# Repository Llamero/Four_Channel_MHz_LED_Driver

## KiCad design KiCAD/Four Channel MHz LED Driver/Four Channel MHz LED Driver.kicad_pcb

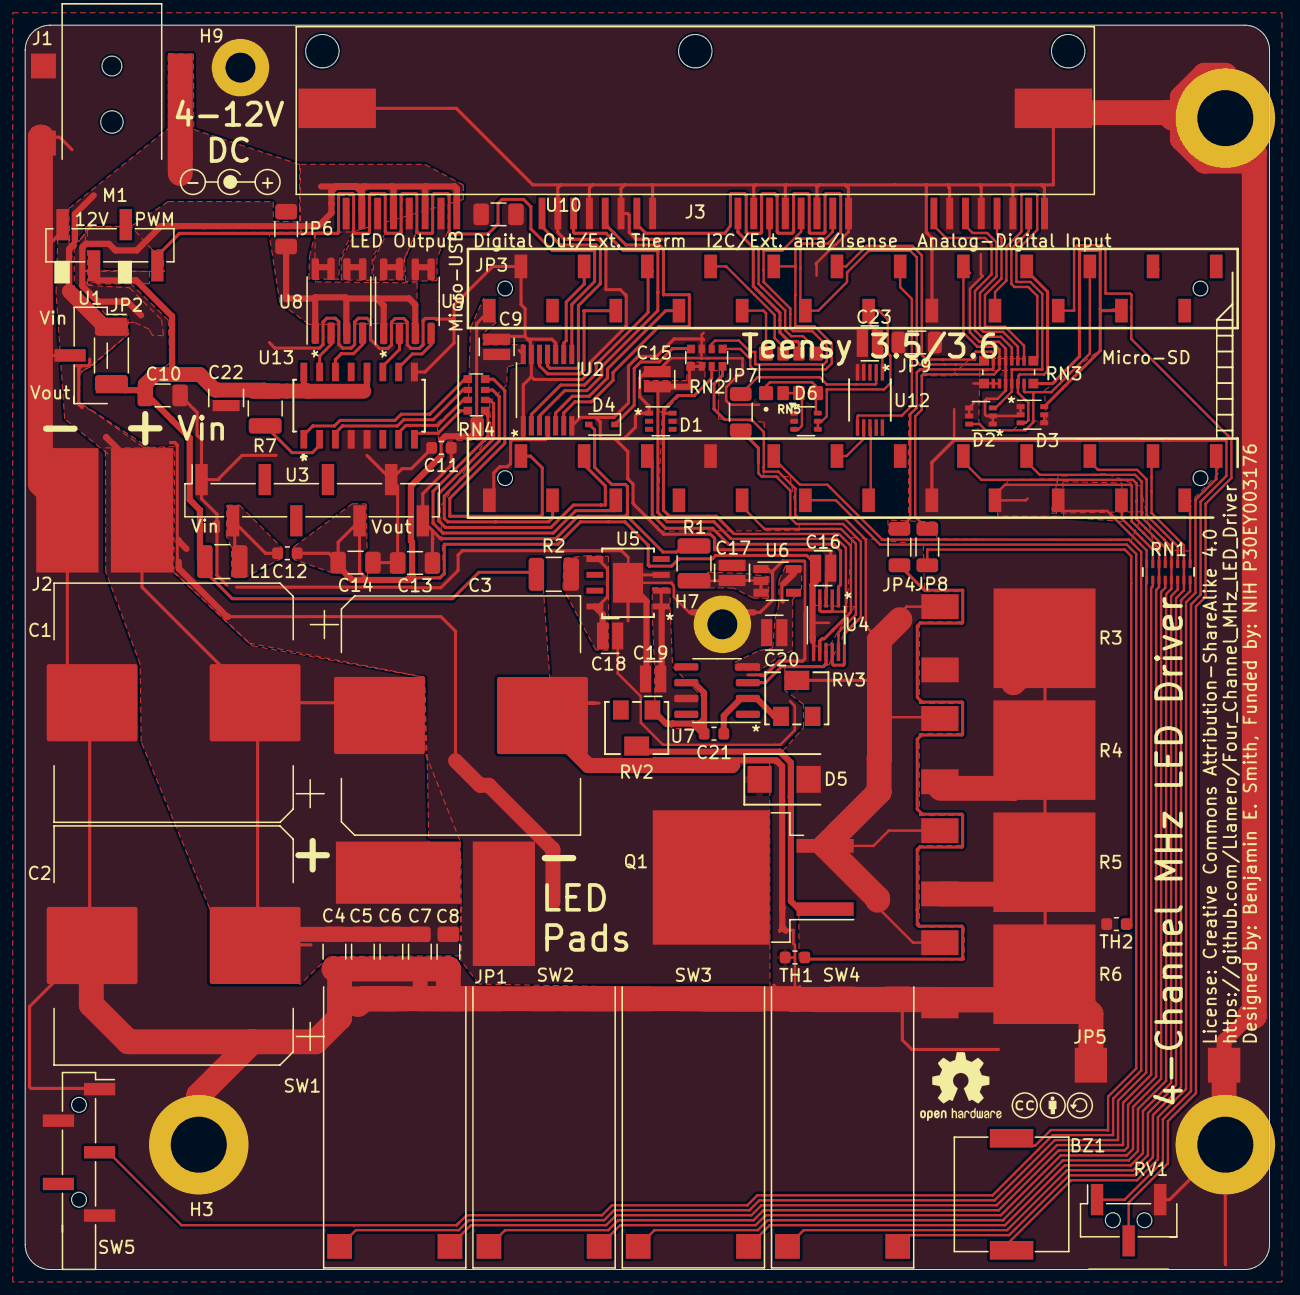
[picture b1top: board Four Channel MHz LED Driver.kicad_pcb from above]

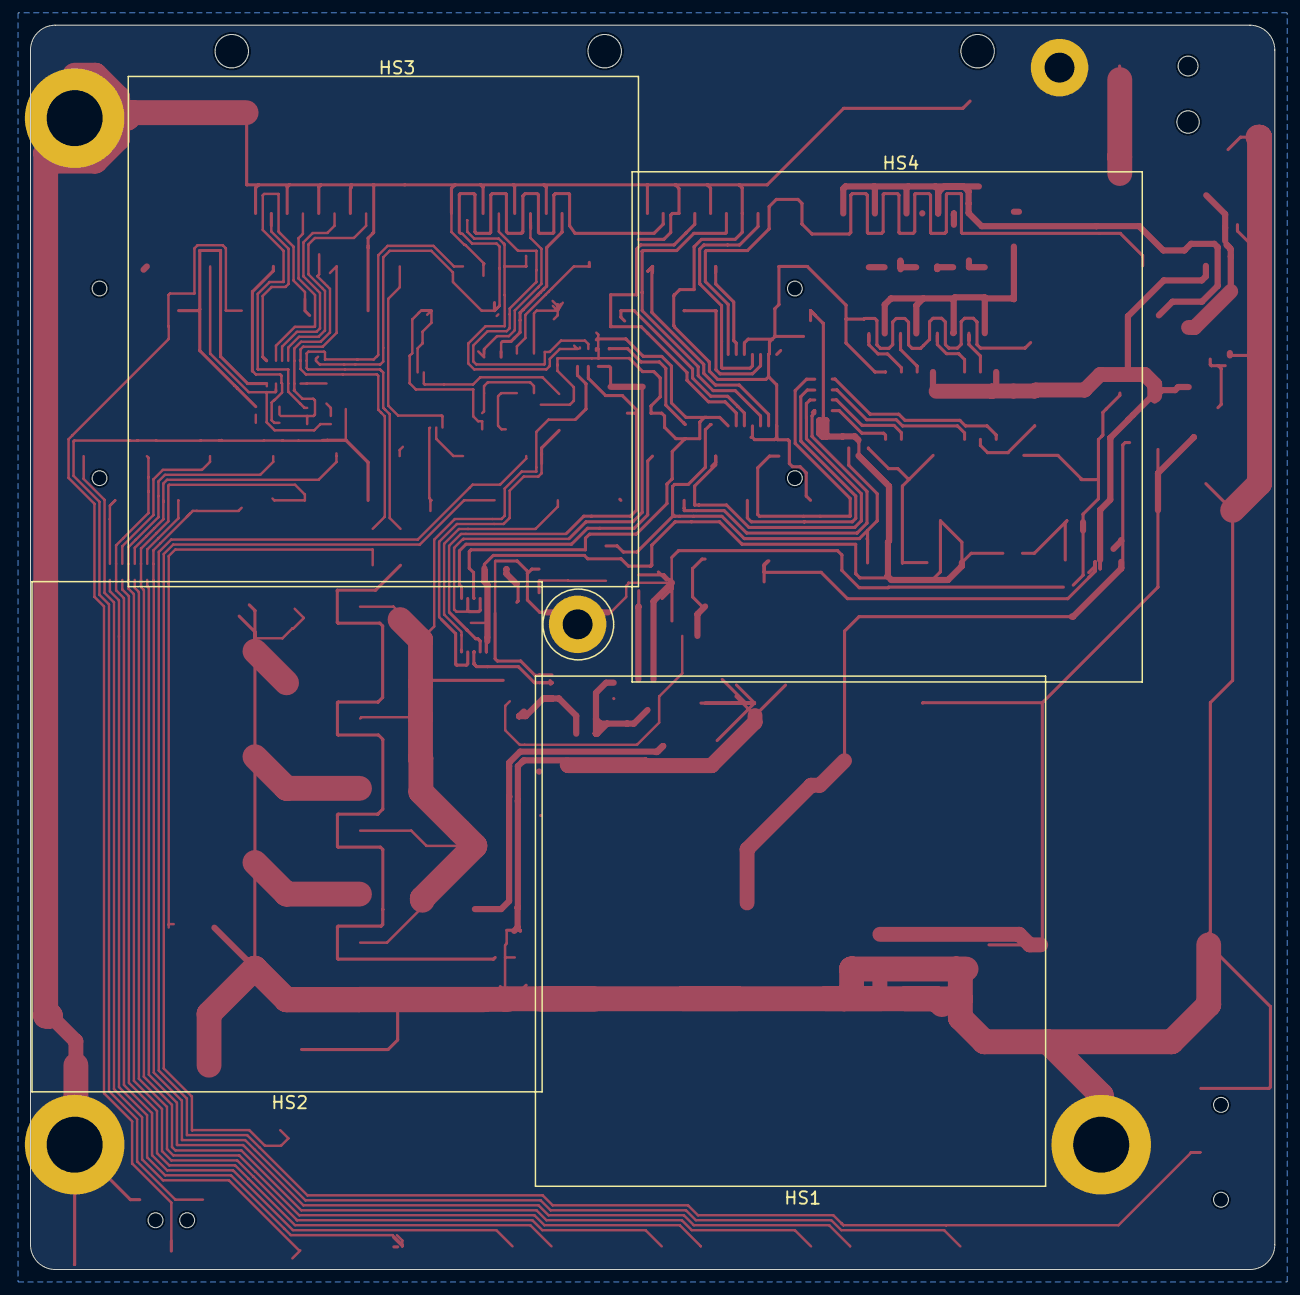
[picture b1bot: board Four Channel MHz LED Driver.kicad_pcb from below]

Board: 2 copper layers, 100.0 x 100.0 mm, 89 parts (4 on the bottom side), 86 nets.

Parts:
BZ1: CPT-2016-75-SMT-TR; SMT-0940-T-3V-R_9x9_alarm
C1, C2, C3: 7500uF; CP_Elec_18x22-EEE-FK1C752SV
C4, C5, C6, C7, C8, C10, C13, C14: 47uF; C_1206_3216Metric
C9, C15, C16, C17, C18, C19, C20, C22, C23: 2.2uF; 0508_Capacitor
C11, C12, C21: 2200pF; C_0603_1608Metric
D1, D2, D3, D6: BAT54BRW; SOT-363_SC-70-6
D4: D_Zener; D_SOD-323
D5: TVS_Diode; DO-214AA
H3: MountingHole_Pad; NF-A9_with_standoffs_and_bolts
H7, H9: MountingHole_Pad; M2_standoff_ground_via
HS1, HS2, HS3, HS4: HS-PCB; Heatsink_910-40-2-23-2-B-0
J1: Barrel_Jack_Switch; DC-jack_54-00165
J2: Conn_01x02_Female; Wire_Pad
J3: 8P8C_Shielded_x4; RJ45_x4-RJSSE-5380-04
JP1: LED wire; L-Wire_Pad
JP2: Jumper_NC_Small; R_2010_5025Metric
JP3, JP4, JP6, JP7, JP8, JP9: Jumper_NC_Small; R_1206_3216Metric
JP5: Jumper_NC_Small; 20A_shunt_5104
L1: 10uH; L_1210_3225Metric
LOGO1: CC license; Creative_commons_license
LOGO2: Jack Polarity; Polarity_Center_Positive
LOGO3: OSHW Logo; OSHW-Logo2_7.3x6mm_SilkScreen
M1: Fan_4pin; 4-pin_fan_SMD
Q1: SUM70060E; TO-263-2
R1, R2, R7: 12; R_1210_3225Metric
R3, R4, R5, R6: 5; TO-252_resistor
RN1: 150; EXB-2HV151JV-1605x8
RN2, RN4: 200; R_Array_Convex_4x0612
RN3: 4.7k; 1506-EXB-2HV472JV-for_2_oz_pour
RN5: 4.7k; RESCAXS127P508X320X70-8N
RV1: R_POT; Pot_with_header
RV2, RV3: R_POT_TRIM; 3224W-1-502E
SW1, SW2, SW3, SW4: Pushbutton_with_LED; Pushbutton_LED-ELUMOATHQ3C12
SW5: SW_SPDT; 1x5_header_SSM-105-L-SV-BE-LC
TH1, TH2: Thermistor; R_0603_1608Metric
U1: 12V boost; 12V_DC-DC_with_header_2117
U2: SN74LV4T125PWR; SN74LV4T125
U3: DPBW06F-05; DPBW06F-05_with_header
U4: TMUX1204DGSR
U5: BDJ0GA5WEFJ-E2
U6: ADP7182AUJZ-1.8-R7; TSOT-23-5
U7: LT6200CS8-10; SOIC-8_3.9x4.9mm_P1.27mm
U8, U9: IRF9358TRPBF; SO-8_3.9x4.9mm_P1.27mm
U10: Teensy4.1; Teensy_4_1_with_headers
U12: DAC80501ZDGSR; DGS10_TEX
U13: EL7457CSZ-T7; EL7457CS

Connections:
/3.3V: C23.2, D1.5, D2.4, D2.5, D3.4, D3.5, D6.4, D6.5, RN3.9 (R8.2), RN3.10 (R7.2), RN3.11 (R6.2), RV1.1, U10.8 (6_OUT1D), U10.15 (3V3), U10.36 (14_A0_TX3_SPDIF_OUT), U10.46 (3V3), U12.1 (VDD)
/5V: C9.1, C12.1, C14.2, C16.2, U2.14 (VCC), U3.6 (+Vout), U4.5 (EN), U4.6 (VDD), U10.48 (VIN)
/5V_fan_PWM: M1.4 (PWM), U2.8 (3Y)
/10V-analog: C19.1, U5.1 (VO), U5.2 (FB), U7.7 (V+)
/12V: C10.2, C22.2, JP2.1, L1.1, M1.2 (+), R2.1, R7.1, U1.3 (OUT), U13.12 (VH), U13.16 (VS+)
/-0.25V_analog: C15.1, RN2.5 (R4.2), RN2.6 (R3.2), U4.2 (S1), U4.4 (S3)
/-1.8V-analog: C20.2, U6.5 (VOUT), U7.4 (V-)
/-5V: C11.1, C13.1, D4.2 (A), R1.1, U3.8 (-Vout)
/A-D_input_1: D2.3, RN3.13 (R4.2), U10.32 (40_A16)
/A-D_input_2: D3.3, RN3.14 (R3.2), U10.31 (39_MISO1_OUT1A)
/A-D_input_3: D2.6, RN3.15 (R2.2), U10.29 (37_CS)
/A-D_input_4: D3.6, RN3.16 (R1.2), U10.28 (36_CS)
/A-D_input_5: D6.3, RN5.2 (R2.1), RN5.3 (R3.1), RN5.7 (R2.2), U10.41 (19_A5_SCL)
/A-D_input_6: D6.6, RN5.1 (R1.1), RN5.4 (R4.1), RN5.8 (R1.2), U10.40 (18_A4_SDA)
/Analog_select: U4.10 (A1), U10.9 (7_RX2_OUT1A)
/Button1: RN1.8 (R8.1), RN1.9 (R8.2), SW1.4 (NC), U10.19 (27_A13_SCK1)
/Button2: RN1.6 (R6.1), RN1.11 (R6.2), SW2.4 (NC), U10.17 (25_A11_RX6_SDA2)
/Button3: RN1.4 (R4.1), RN1.13 (R4.2), SW3.4 (NC), U10.18 (26_A12_MOSI1)
/Button4: RN1.2 (R2.1), RN1.15 (R2.2), SW4.4 (NC), U10.22 (30_CRX3)
/CS: U10.12 (10_CS_MQSR), U12.7 (*SYNC/A0)
/External_5V_2: U2.2 (1A), U10.43 (21_A7_RX5_BCLK1)
/External_5V_3: U2.5 (2A), U10.42 (20_A6_TX5_LRCLK1)
/External_5V_PWM1: U2.12 (4A), U10.44 (22_A8_CTX1)
/External_thermistor: J3.15, RN3.8 (R8.1), U10.38 (16_A2_RX4_SCL1)
/Interline_PWM: U4.1 (A0), U10.6 (4_BCLK2)
/Internal_fan_PWM: U2.9 (3A), U10.45 (23_A9_CRX1_MCLK1)
/Isense: D5.2 (A), Q1.3 (S), R3.1, R4.1, R5.1, R6.1, RN2.8 (R1.2), RV3.2
/Isense_internal: J3.23, RN2.1 (R1.1), U10.39 (17_A3_TX4_SDA1)
/LED1: RN1.7 (R7.1), U10.21 (29_TX7)
/LED2: RN1.5 (R5.1), U10.16 (24_A10_TX6_SCL2)
/LED3: RN1.3 (R3.1), U10.20 (28_RX7)
/LED4: RN1.1 (R1.1), U10.23 (31_CTX3)
/LED-: D5.1 (K), J3.2, J3.4, J3.6, J3.8, JP1.2, Q1.2 (D)
/LED_pot: RV1.2, U10.30 (38_CS1_IN1)
/MOSFET_temp: JP4.1, JP4.2, RN3.7 (R7.1), TH1.1, U10.37 (15_A1_RX3_SPDIF_IN)
/MOSI: U10.13 (11_MOSI_CTX1), U12.8 (SDIN/SDA)
/OA_input: U4.8 (D), U7.3 (+)
/Over_temp_alarm1: BZ1.1, U10.24 (32_OUT1B)
/Over_temp_alarm2: BZ1.2, U10.11 (9_OUT1C)
/Relay1: RN4.1 (R1.1), U10.5 (3_LRCLK2)
/Relay2: RN4.2 (R2.1), U10.4 (2_OUT2)
/Relay3: RN4.3 (R3.1), U10.3 (1_TX1_CTX2_MISO1)
/Relay4: RN4.4 (R4.1), U10.2 (0_RX1_CRX2_CS1)
/Resistor_temp: JP8.1, JP8.2, RN3.6 (R6.1), TH2.1, U10.33 (41_A17)
/SCK: U10.35 (13_SCK_LED), U12.6 (SCLK/SCL)
/Toggle_switch: SW5.3 (C), U10.10 (8_TX2_IN1)
/Vcc: JP6.2, U8.1 (S1), U8.3 (S2), U9.1 (S1), U9.3 (S2)
/Vin: C1.1, C2.1, C3.1, C4.2, C5.2, C6.2, C7.2, C8.2, J1.1, J2.2, JP1.1, JP2.2, JP6.1, U1.1 (IN)
/external_analog: D1.6, RN2.7 (R2.2), U4.7 (S4)
/internal_analog: JP7.1, U4.9 (S2)
GND: C1.2, C2.2, C3.2, C4.1, C5.1, C6.1, C7.1, C8.1, C9.2, C10.1, C11.2, C13.2, C14.1, C15.2, C16.1, C17.2, C18.2, C19.2, C20.1, C22.1, C23.1, D1.1, D2.1, D2.2, D3.1, D3.2, D6.1, D6.2, H3.1, H7.1, H9.1, J1.2, J1.3, J2.1, J3.10, J3.12, J3.14, J3.16, J3.18, J3.20, J3.22, J3.24, J3.26, J3.28, J3.30, J3.32, J3.SH, JP3.1, JP3.2, JP5.1, JP5.2, JP9.1, JP9.2, M1.1 (-), R3.2, R4.2, R5.2, R6.2, RN2.3 (R3.1), RN3.5 (R5.1), RN3.12 (R5.2), RV1.3, SW1.1 (K), SW1.2 (NO), SW1.3 (COM), SW2.1 (K), SW2.2 (NO), SW2.3 (COM), SW3.1 (K), SW3.2 (NO), SW3.3 (COM), SW4.1 (K), SW4.2 (NO), SW4.3 (COM), SW5.1 (A), SW5.2 (B), SW5.5 (GND), TH1.2, TH2.2, U1.2 (GND), U2.1 (1!OE), U2.4 (2!OE), U2.7 (GND), U2.10 (3!OE), U2.13 (4!OE), U3.1 (Vin-), U3.7 (Com), U4.3 (GND), U5.3 (GND), U5.EPAD, U6.1 (GND), U10.1 (GND), U10.34 (GND), U10.47 (GND), U12.4 (AGND), U12.5 (SPI2C), U13.4 (VL), U13.5 (GND), U13.9 (VS-)
unnamed: C21.1, RV2.1, U7.6
unnamed: D4.1 (K), RN2.4 (R4.1)
unnamed: J3.1, U8.7 (D1), U8.8 (D1)
unnamed: J3.3, U8.5 (D2), U8.6 (D2)
unnamed: J3.5, U9.7 (D1), U9.8 (D1)
unnamed: J3.7, U9.5 (D2), U9.6 (D2)
unnamed: Q1.1 (G), RV2.2
unnamed: RN1.16 (R1.2), SW4.5 (A)
unnamed: RN1.14 (R3.2), SW3.5 (A)
unnamed: RN1.12 (R5.2), SW2.5 (A)
unnamed: RN1.10 (R7.2), SW1.5 (A)
unnamed: J3.21, RN2.2 (R2.1)
unnamed: J3.31, RN3.1 (R1.1)
unnamed: J3.29, RN3.2 (R2.1)
unnamed: J3.27, RN3.3 (R3.1)
unnamed: J3.25, RN3.4 (R4.1)
unnamed: RN4.8 (R1.2), U13.8 (IND)
unnamed: RN4.7 (R2.2), U13.7 (INC)
unnamed: RN4.6 (R3.2), U13.3 (INB)
unnamed: RN4.5 (R4.2), U13.1 (INA)
unnamed: J3.17, RN5.6 (R3.2)
unnamed: J3.19, RN5.5 (R4.2)
unnamed: J3.11, U2.3 (1Y)
unnamed: J3.13, U2.6 (2Y)
unnamed: J3.9, U2.11 (4Y)
unnamed: C12.2, L1.2, U3.2 (Vin+)
unnamed: C18.1, R2.2, U5.5 (EN), U5.8 (VCC)
unnamed: C17.1, R1.2, U6.2 (VIN), U6.3 (EN)
unnamed: C21.2, RV3.1, U7.2 (-)
unnamed: JP7.2, U12.2 (VOUT)
unnamed: R7.2, U13.2 (OE)
unnamed: U8.2 (G1), U13.15 (OUTA)
unnamed: U8.4 (G2), U13.14 (OUTB)
unnamed: U9.2 (G1), U13.11 (OUTC)
unnamed: U9.4 (G2), U13.10 (OUTD)

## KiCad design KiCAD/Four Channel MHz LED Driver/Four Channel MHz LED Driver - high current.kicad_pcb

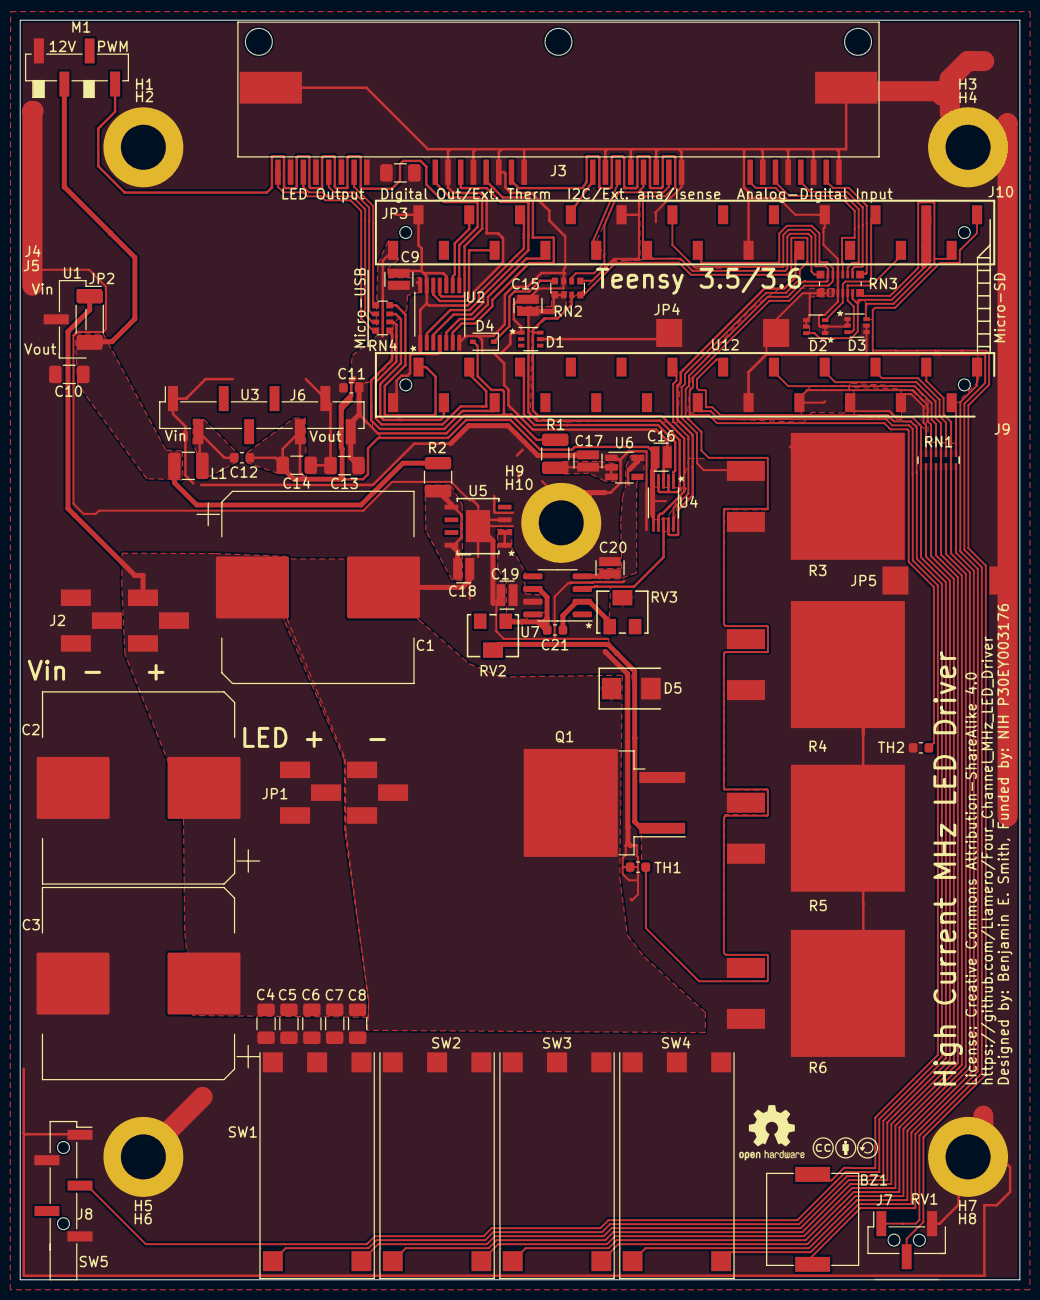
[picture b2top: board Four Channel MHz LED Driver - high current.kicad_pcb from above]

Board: 2 copper layers, 100.0 x 126.0 mm, 85 parts (0 on the bottom side), 71 nets.

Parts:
BZ1: CPT-2016-75-SMT-TR; SMT-0940-T-3V-R_9x9_alarm
C1, C2, C3: 7500uF; CP_Elec_18x22-EEE-FK1C752SV
C4, C5, C6, C7, C8, C10, C13, C14: 47uF; C_1206_3216Metric
C9, C15, C16, C17, C18, C19, C20: 2.2uF; 0508_Capacitor
C11, C12, C21: 2200pF; C_0603_1608Metric
D1, D2, D3: BAT54BRW; SOT-363_SC-70-6
D4: D_Zener; D_SOD-323
D5: TVS_Diode; DO-214AA
H1, H2, H4, H5, H6, H8, H9, H10: MountingHole_Pad; Ref_only
H3: MountingHole_Pad; NF-A9_with_standoffs_and_bolts_high_current
H7: MountingHole_Pad; M4_bolt_hole
HS1: HS-PCB; Ref_only
J2: Conn_01x02_Female; 4928TR-power
J3: 8P8C_Shielded_x4; RJ45_x4-RJSSE-5380-04
J4: Conn_01x03_Male; Ref_only
J5, J7: Conn_01x03_Female; Ref_only
J6: Conn_01x08_Female; Ref_only
J8: Conn_01x05_Female; Ref_only
J9, J10: Conn_01x24_Female; Ref_only
JP1: LED wire; 4928TR-power
JP2: Jumper_NC_Small; R_2010_5025Metric
JP3: Jumper_NC_Small; R_1206_3216Metric
JP4, JP5: Jumper_NC_Small; 20A_shunt_5104
L1: 10uH; L_1210_3225Metric
LOGO1: CC license; Creative_commons_license
LOGO3: OSHW Logo; OSHW-Logo2_7.3x6mm_SilkScreen
M1: Fan_4pin; 4-pin_fan_SMD
Q1: SUM70060E; TO-263-2
R1, R2: 12; R_1210_3225Metric
R3, R4, R5, R6: 0.2; Rideon_PFS35_resistor
RN1: 150; EXB-2HV151JV-1605x8
RN2, RN4: 200; R_Array_Convex_4x0612
RN3: 4.7k; 1506-EXB-2HV472JV-for_2_oz_pour
RV1: R_POT; Pot_with_header
RV2, RV3: R_POT_TRIM; 3224W-1-502E
SW1, SW2, SW3, SW4: Pushbutton_with_LED; Pushbutton_LED-ELUMOATHQ3C12
SW5: SW_SPDT; 1x5_header_SSM-105-L-SV-BE-LC
TH1, TH2: Thermistor; R_0603_1608Metric
U1: 12V boost; 12V_DC-DC_with_header_2117
U2: SN74LV4T125PWR; SN74LV4T125
U3: DPBW06F-05; DPBW06F-05_with_header
U4: TMUX1204DGSR
U5: BDJ0GA5WEFJ-E2
U6: ADP7182AUJZ-1.8-R7; TSOT-23-5
U7: LT6200CS8-10; SOIC-8_3.9x4.9mm_P1.27mm
U12: Teensy3.6; Teensy_3_6_with_headers

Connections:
/3.3V: D2.4, D2.5, D3.4, D3.5, JP4.2, RN3.9, RN3.10, RN3.11, RV1.1, U12.15
/5V: C9.1, C12.1, C14.2, C16.2, U2.14, U3.6, U4.5, U4.6, U12.53
/5V_fan_PWM: M1.4, U2.8
/10V-analog: C19.1, U5.1, U5.2, U7.7
/12V: C10.2, JP2.1, L1.1, M1.2, R2.1, U1.3
/-0.25V_analog: C15.1, RN2.5, RN2.6, U4.2, U4.4
/-1.8V-analog: C20.2, U6.5, U7.4
/-5V: C11.1, C13.1, D4.2, R1.1, U3.8
/A-D_input_1: D2.3, RN3.13, U12.34
/A-D_input_2: D3.3, RN3.14, U12.33
/A-D_input_3: D2.6, RN3.15, U12.32
/A-D_input_4: D3.6, RN3.16, U12.31
/Analog_select: U4.10, U12.12
/Button1: RN1.8, RN1.9, SW1.4, U12.19
/Button2: RN1.6, RN1.11, SW2.4, U12.17
/Button3: RN1.4, RN1.13, SW3.4, U12.18
/Button4: RN1.2, RN1.15, SW4.4, U12.22
/External_5V_PWM1: U2.12, U12.49
/External_5V_PWM2: U2.2, U12.48
/External_5V_PWM3: U2.5, U12.47
/External_thermistor: J3.15, RN3.8, U12.43
/Interline_PWM: U4.1, U12.6
/Internal_fan_PWM: U2.9, U12.50
/Isense: D5.2, Q1.3, R3.1, R4.1, R5.1, R6.1, RN2.8, RV3.2
/Isense_internal: J3.23, RN2.1, U12.44
/LED1: RN1.7, U12.21
/LED2: RN1.5, U12.16
/LED3: RN1.3, U12.20
/LED4: RN1.1, U12.23
/LED-: D5.1, JP1.2, Q1.2
/LED_pot: RV1.2, U12.30
/MOSFET_temp: RN3.7, TH1.1, U12.42
/OA_input: U4.8, U7.3
/Over_temp_alarm1: BZ1.1, U12.24
/Over_temp_alarm2: BZ1.2, U12.13
/Relay1: RN4.1, U12.5
/Relay2: RN4.2, U12.4
/Relay3: RN4.3, U12.3
/Relay4: RN4.4, U12.2
/Resistor_temp: RN3.6, TH2.1, U12.41
/SCL0: J3.17, U12.46
/SDA0: J3.19, U12.45
/Toggle_switch: SW5.3, U12.14
/Vin: C1.1, C2.1, C3.1, C4.2, C5.2, C6.2, C7.2, C8.2, J2.2, JP1.1, JP2.2, U1.1
/external_analog: D1.6, RN2.7, U4.7
/internal_analog: U4.9, U12.37
GND: C1.2, C2.2, C3.2, C4.1, C5.1, C6.1, C7.1, C8.1, C9.2, C10.1, C11.2, C13.2, C14.1, C15.2, C16.1, C17.2, C18.2, C19.2, C20.1, D1.1, D2.1, D2.2, D3.1, D3.2, H3.1, H7.1, J2.1, J3.2, J3.4, J3.6, J3.8, J3.10, J3.12, J3.14, J3.16, J3.18, J3.20, J3.22, J3.24, J3.26, J3.28, J3.30, J3.32, J3.SH, JP3.1, JP3.2, JP5.1, JP5.2, M1.1, R3.2, R4.2, R5.2, R6.2, RN2.3, RN3.5, RN3.12, RV1.3, SW1.1, SW1.2, SW1.3, SW2.1, SW2.2, SW2.3, SW3.1, SW3.2, SW3.3, SW4.1, SW4.2, SW4.3, SW5.1, SW5.2, SW5.5, TH1.2, TH2.2, U1.2, U2.1, U2.4, U2.7, U2.10, U2.13, U3.1, U3.7, U4.3, U5.3, U5.EPAD, U6.1, U12.1, U12.36, U12.39, U12.52
unnamed: C12.2, L1.2, U3.2
unnamed: C17.1, R1.2, U6.2, U6.3
unnamed: C18.1, R2.2, U5.5, U5.8
unnamed: C21.1, RV2.1, U7.6
unnamed: C21.2, RV3.1, U7.2
unnamed: D1.5, JP4.1
unnamed: D4.1, RN2.4
unnamed: J3.1, RN4.8
unnamed: J3.3, RN4.7
unnamed: J3.5, RN4.6
unnamed: J3.7, RN4.5
unnamed: J3.9, U2.11
unnamed: J3.11, U2.3
unnamed: J3.13, U2.6
unnamed: J3.21, RN2.2
unnamed: J3.25, RN3.4
unnamed: J3.27, RN3.3
unnamed: J3.29, RN3.2
unnamed: J3.31, RN3.1
unnamed: Q1.1, RV2.2
unnamed: RN1.10, SW1.5
unnamed: RN1.12, SW2.5
unnamed: RN1.14, SW3.5
unnamed: RN1.16, SW4.5

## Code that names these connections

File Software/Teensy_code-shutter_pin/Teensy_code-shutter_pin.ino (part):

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  for(size_t a=0; a==status_index; a++) checkStatus(); //Perform full round of status checks to get starting status of driver
  
  digitalWriteFast(pin.INTERLINE, LOW);
  digitalWriteFast(pin.ANALOG_SELECT, LOW);
  digitalWriteFast(pin.FAN_PWM, LOW);
  analogWrite(pin.DAC0, 0);
}
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    }
  }
  else{ //If using external analog
    pinMode(pin.ANALOG_SELECT, OUTPUT);
    external_analog = true;
    pinMode(pin.INTERLINE, OUTPUT);
    digitalWriteFast(pin.ANALOG_SELECT, HIGH); //Set external analog input
    digitalWriteFast(pin.INTERLINE, HIGH); //Set LED on
    while(!current_status.s.mode && sync.s.mode == 1 && sync.s.analog_mode != 2 && !update_flag) checkStatus();
  }
  quit:
    pinMode(pin.ANALOG_SELECT, OUTPUT);
    digitalWriteFast(pin.ANALOG_SELECT, LOW); //Set internal analog input
    external_analog = false;
    interrupts();
    analogWriteFrequency(pin.INTERLINE, pin.LED_FREQ); //Restore the interline timer to its defaul value: https://www.pjrc.com/teensy/td_pulse.html
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    pwm_freq *= 2; //Double the pwm freq since the LED flashes twice per period
    pwm_ratio *= 2; //Double the pwm ratio since the ratio is now delay[1] / (0.5 * mirror period)
  }
  analogWriteFrequency(pin.INTERLINE, pwm_freq); //Set interline PWM freq to match mirror freq, also sets analog_select PWM freq (on same timer): https://www.pjrc.com/teensy/td_pulse.html
  
  if(sync.s.confocal_mirror_period > unidirectional_status_window) unidirectional_status_window = sync.s.confocal_mirror_period - unidirectional_status_window;
  else unidirectional_status_window = 0;
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    while(shutter_state == digitalReadFast(shutter_pin) && !update_flag){ //While shutter state doesn't change and driver still in digital sync mode - checked each time a seq step is complete
      if(sync_step < seq_steps[current_status.s.state]){ //If the end of the sequence list has not been reached
        if(sync.s.confocal_mode[current_status.s.state] == 3){ //If sync uses external analog , set external analog pin HIGH
          pinMode(pin.ANALOG_SELECT, OUTPUT);
          external_analog = true;
          digitalWriteFast(pin.ANALOG_SELECT, HIGH); //Set external analog input
        }
        else{ //For all other modes, set led intensity to new values
          pinMode(pin.ANALOG_SELECT, OUTPUT);
          external_analog = false;
          digitalWriteFast(pin.ANALOG_SELECT, LOW); //Set internal analog input
          updateIntensity(); 
        }
        
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  quit:
    analogWriteFrequency(pin.INTERLINE, pin.LED_FREQ); //Restore the interline timer to its defaul value: https://www.pjrc.com/teensy/td_pulse.html
    interrupts();
    pinMode(pin.ANALOG_SELECT, OUTPUT);
    digitalWriteFast(pin.ANALOG_SELECT, LOW);
    external_analog = false;
}

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    while(shutter_state == digitalReadFast(shutter_pin) && !update_flag){ //While shutter state doesn't change and driver still in digital sync mode - checked each time a seq step is complete
      if(sync_step < seq_steps[current_status.s.state]){ //If the end of the sequence list has not been reached
        if(sync.s.confocal_mode[current_status.s.state] == 3){ //If sync uses external analog , set external analog pin HIGH
          pinMode(pin.ANALOG_SELECT, OUTPUT);
          external_analog = true;
          digitalWriteFast(pin.ANALOG_SELECT, HIGH); //Set external analog input
        }
        else{ //For all other modes, set led intensity to new values
          pinMode(pin.ANALOG_SELECT, OUTPUT);
          external_analog = false;
          digitalWriteFast(pin.ANALOG_SELECT, LOW); //Set internal analog input
          updateIntensity(); 
        }      

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  quit:
    analogWriteFrequency(pin.INTERLINE, pin.LED_FREQ); //Restore the interline timer to its defaul value: https://www.pjrc.com/teensy/td_pulse.html
    interrupts();
    pinMode(pin.ANALOG_SELECT, OUTPUT);
    digitalWriteFast(pin.ANALOG_SELECT, LOW);
    external_analog = false;
    pinMode(shutter_pin, INPUT_DISABLE); //Set shutter input pin to input
    pinMode(pin.INPUTS[0], INPUT_DISABLE); //Set sync input pin to input
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  switch(status_index){
    case 0: //Check driver temperatures - 3.68 µs
      status_index++;
      analogRead(pin.MOSFET_TEMP);
      current_status.s.temp[0] = analogRead(pin.MOSFET_TEMP);
      break;
    case 1:
      status_index++;
      analogRead(pin.RESISTOR_TEMP);
      current_status.s.temp[1] = analogRead(pin.RESISTOR_TEMP);
      break;
    case 2: //Check external thermistor with rolling average - 3.1 µs to 4.5 µs max
      status_index++;
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      status_index++;
      if(current_status.s.mode){ //If in manual mode, use internal analog
        external_analog = false;
        digitalWriteFast(pin.ANALOG_SELECT, LOW); //Set external analog input
      }
      else{ //If in sync mode
        if((sync.s.mode == 0 && sync.s.digital_mode[current_status.s.state] == 3) || (sync.s.mode == 2 && sync.s.confocal_mode[current_status.s.state] == 3) || (sync.s.mode == 1 && sync.s.analog_mode == 2)){ //If state requires ext. analog
          external_analog = true;
          pinMode(pin.ANALOG_SELECT, OUTPUT);
          digitalWriteFast(pin.ANALOG_SELECT, HIGH); //Set external analog input
        }
      }
      break;
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    }
    active_channel = current_status.s.led_channel;

    digitalWriteFast(pin.ANALOG_SELECT, external_analog); //Set external analog input
    if(external_analog){
      pinMode(pin.INTERLINE, OUTPUT); //ensure pin is disconnected from PWM bus
      analogWrite(pin.DAC0, 0);
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    memcpy(stored_config.byte_buffer, conf.byte_buffer, sizeof(stored_config.byte_buffer)); //Store copy of saved configuration
    memcpy(conf.byte_buffer, buffer, sizeof(conf.byte_buffer)); //Load temp configuration
    analogWrite(pin.INTERLINE, 0); //Turn off LED
    digitalWriteFast(pin.ANALOG_SELECT, LOW); //Set to internal analog
    pinMode(pin.ISENSE, INPUT);
    temp_size = 1; //Initialize temp_buffer index after prefix
    for(int a=0; a<4; a++){
      if(conf.c.led_active[a]){ //If LED channel is active
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        current_status.s.mode = 1; //Assume manual mode to override sync related intensities
        updateIntensity();
        delay(10); //Wait for current and SSRs to settle
        analogRead(pin.ISENSE); //Clear adc
        current_measurement = 0;
        for(int b=0; b<n_samples; b++) current_measurement += analogRead(pin.ISENSE);
        analogWrite(pin.INTERLINE, 0);
        current_array[a] = (float) current_measurement / (float) n_samples; //Divide by n_samples to get average current
        if(current_array[a] + (0.5/3.3)*65535 < conf.c.current_limit[a] || current_array[a] - (0.5/3.3)*65535 > conf.c.current_limit[a]){ //Disable channel if Isense voltage is outside DAC voltage +/- 0.5V to prevent damage to op-amp
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    usb.send((const unsigned char*) temp_buffer, sizeof(enable_array)+1);
    memcpy(current_status.byte_buffer, stored_status.byte_buffer, sizeof(stored_status.byte_buffer)); //Restore status
    memcpy(conf.byte_buffer, stored_config.byte_buffer, sizeof(stored_config.byte_buffer)); //Restore configuraiton
    digitalWriteFast(pin.ANALOG_SELECT, external_analog); //Restore analog input selection
    updateIntensity(); //Restore led intensity
  }
  else{
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
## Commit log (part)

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2020-08-12 SEPIC BGA supply
2020-08-15 Add Spice models
2020-08-19 First draft of Teensy pin allocation
2020-08-19 Update license
2020-08-20 Add LED connectors switch to RJ45 for IO
2020-08-22 And internal analog bypass jumpers
2020-08-22 Removed LED combine jumpers
    I removed the LED combining jumpers as the only case where they would be helpgul is if the driver is in a high current/power mode. In this state, parallel wiring is likely better anyway to reduce the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
2020-08-22 minimal
2020-08-22 Add label to 12V SEPIC pins
    Added labels to pins on PCB to that if people can bypass the supply with a wire.
2020-08-24 Overhaul
    1) Reduced impedance on external analog as the op-amp inputs can sink as much as 50uA, so reduced impedance reduces voltage error.
    2) Removed digipot for the same reason as the impedance of the digipot can cause a voltage error due to the op-amp input sink. This also simplifies the circuit.
    3) Switched the DAC to the 12-bit version to allow current limiting via the DAC.
    4) Swith out 5V LDO for 5V Zener voltage reference for DAC for better RC filtering and accurate reference.
    5) Switched -0.2V divider to a 4.7V zener to allow greater sink current from op-amp with minimal shift in voltage.
    6) Added external fan PWM.
2020-08-25 Add more bypass
2020-08-26 IO and LCD
    1) Used the spare output to add external output for the overheat alarm. This will allow external equipment to know if the device overheated and turned off the LED. Useful for overnight runs.
    2) Added an LCD display
    3) Added closed jumpers on the shared MISO/alarm line so that the LCD can be disconnected from the piezo device if it turns out that normal use is audible.
2020-08-26 Put current output inside voltage divider
    If the cirrent sense voltage is directly sent externally, and accidental short would both cause full current to go through that channel (potentially destroying the LED and driver channel) but also th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
    The impedance of the divider was therefore also reduced to 1k, so that 10 MHz signals will be minimally attenuated.
2020-08-27 20mm heatsinks
2020-08-29 Rough layout
2020-09-05 Starting layout
2020-09-07 Relays connected
2020-09-07 Fan updated with bolts
2020-09-07 stacked standoffs and high current jumpers added
2020-09-08 Switch connected to 5V
2020-09-08 Replace fan mount holes with PTH for DRC and FR4 compatibility
2020-09-08 More pours added
2020-09-09 Update just before swapping ethernet jacks
2020-09-09 DRC check after ADIO connection
2020-09-10 Thicker guard boundary
2020-09-10 Straightened PWM tracks
2020-09-10 Improved SSR traces to minimize inductance
2020-09-10 More trace optimization
2020-09-11 Fix PCB after cleaned up schematic
2020-09-11 Fix footprints and position silkscreen labels
2020-09-11 Cap courtyard fixed
2020-09-11 Courtyard fix and track optimization
2020-09-11 more HS optimization
2020-09-11 Analog pours improvement
2020-09-11 bypass pour optimization
2020-09-11 Fixed error of disconnected FB pin on 10V LDO and improved cap placement
2020-09-12 Switch to 200 omh for relay to keep max current below 9 mA
2020-09-12 Fix back silkscreen lines
2020-09-12 Improved compensation cap placement
2020-09-13 Switch 150 ohm 4-pack for 200 ohm 4-pack to remove unique part
2020-09-13 Rolocate GND jumper to widen Vin and LED- pours for 4A capability
2020-09-14 Updated electrolytic cap footprints
2020-09-14 Add panel ground to toggle switch
2020-09-15 Add thermal relief to TVS diode
2020-11-03 Fix KiCAD footprint error with 1206 rarray (0612 is really 1206)
2020-11-05 Revision 2 submitted for order
2020-11-05 Add forward and reverse NTC - Temp conversion
2020-11-15 Add Python GUI
2020-11-17 Code starts in main()
2020-11-19 Add QDarkStyleSheet to GUI
    https://github.com/ColinDuquesnoy/QDarkStyleSheet
2020-11-20 Add status window to GUI
2020-11-21 Added calibration tab
2020-11-24 Add message window
2020-12-02 Fix config panel fan temp columns
2020-12-02 Clean up schematic
2020-12-10 Start adding tool tips
2020-12-21 Analog sync done - partway through confocal sync
2020-12-22 Syncs complete
2020-12-23 config widgets labelled
2020-12-29 Main, sync, and configure tool-tips are complete
2020-12-29 Menu and button groups complete
2020-12-31 Keep font size consistent when switching style sheets
2021-01-13 Start of madel as dictionary
2021-01-14 Preliminary load sequence function with error checking
2021-01-15 Save and load sequence fundtions ported to package
2021-01-15 Start event mapping
    Tried to use eval() within for-loop to map lambda functions, but ran into unstable behavior so iterable mapping was done by hand instead
2021-01-17 Extra row insert on load fixed
2021-01-17 Removed stomping on self in packages - replace self with gui
2021-01-18 Confocal widget model done - confocal LED active toggle done
2021-01-19 Add load config error message
2021-01-19 Delay3 text and tooltip change with scan mode
2021-01-20 Fan out and sync out channels disable one another
2021-01-20 small reorg
2021-01-20 Replace configure widget calls with model calls
2021-01-20 Interface lock added
2021-01-24 Magic number exchange via cobs running
2021-01-29 Driver code compiles
2021-02-05 Convert libraries to static
2021-02-06 Structs with unions are amazing!
2021-02-06 Remove default aligmnent padding from structs
2021-02-07 Started on GUI code for parsing config byte file
2021-02-08 Add checksum test to config upload
2021-02-08 Disconnect COM port after verification complete
2021-02-09 Config upload and download working!
2021-02-11 Connection menu functional - Serial labels functional
2021-02-14 Start of working seq uploader
    Serial still seems to lock with large files - may need to implement a block by block transfer with reply.
2021-02-14 Successfully streamed 10,000 row seq file
2021-02-15 Stream request is via COBS for consistency
2021-02-16 Conversion of sync to byte array completed
2021-02-19 Untested bytesToSync
2021-02-22 Sync with seq load working, including empty files
2021-02-23 Sync loads - splash screen added
2021-02-23 Seq upload bug fixed
    Timeout bug was because small packets would reduce the timeout with the dynamic timeout feature used for packets. This was fixed by setting a master default timeout, and dynamic timeouts can only be 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
2021-02-23 Fixed recursion typo bug in showmessage in seq library
2021-02-26 Plots status packets
2021-02-28 Knob is synced to status
2021-03-03 Main GUI disables on sync active
2021-03-04 Dial update delay allows smooth rotation with software control
2021-03-04 Add heartbeat feature to inform driver of disconnect
2021-03-06 Initial draft of using custom signal/slot to update status
2021-03-06 Status window created via menu
2021-03-07 Clean disconnect form driver
2021-03-09 Running calibration locks out other tabs
2021-03-10 GUI retains state of skin on next load
2021-03-11 Parse of seg for digital started
2021-03-18 Changes names of confocal widgets to "standby" and "scanning"
2021-03-24 Status and sync windows disconnect and delete themselves on close
2021-03-26 Gui lock state is pickled for subsequent loads
2021-03-31 Cleared -fpermissive warnings - fixed issue with pin.OUTPUTS
    The compiler kept flagging pin::OUTPUTS as not bein a valid reference. Moving the constructor from the .h to the .cpp fixed this issue.
2021-04-07 Fixed bug where a memcpy overflowed
2021-04-07 Pushbuttons implemented including manually entering LED off
2021-04-08 Initial draft of thermal fault implemented
2021-04-10 Fixed bugs with thermal fault in manual mode
2021-04-10 Fixed int crop bug on adc to temp conversion for config download
2021-04-11 Fixed bug blocking tone muting
2021-04-13 Measure period fully implemented
2021-04-14 Test current implemented
2021-04-15 Initial draft of seq loader - partially tested
2021-04-16 Fixed PWM modulation artefact at 100% by setting pin to digital high
2021-04-20 Digital sync tested and working!
2021-04-21 Untested draft of confocal sync written
2021-04-22 First draft of confocal analog sync works!!!
2021-04-24 Fix confocal sync ext analog and scanning PWM bugs
    1) Added step to clear ADC during analog trigger sync
    2) Fixed bug where interline PWM clock cycles was capping at 16-bit even though cast to uint32-t. Instead, I just used floating point casting and the issue was resolved.
    3) Changed seq list over flow action to quitting the sync function rather than just breaking the loop, as this will reset the seq counter.
    4) In updateSeq, I added a specific case for external analog sync, where the PWM is at max, and the DAC is at 0. This allows sync to external analog for the full interline window.
2021-04-24 Fixed bug where seq would improperly load if upload during sync
2021-04-24 Fixed bug where couldn't manual LED off
2021-04-24 Sync now stops immediately on disconnect
2021-04-25 Fixed analog sync freq stability, implemented GUI analog label updates with slider
2021-04-25 Update analog sync labels on boot
2021-04-26 Feedback from Franklin
2021-05-21 RJ45 fixed
2021-06-03 Initial high current design
2021-06-08 high power resistor pads - wide pours
2021-06-17 Allow relay polarity to be changed
2021-08-21 Add final draft of high current enclosure labels
2021-09-16 Fix QtGui to QtWidgets bug
2021-09-17 Fix bug where GUI reports errors when trying to test connections
2021-09-18 Custom sync sequence is now triggerable
2021-10-20 Fix sequence table scaling
2021-12-15 Update guiConfigIO.py
    Fix parentheses typo
2021-12-17 Remove timing code
2021-12-23 UNTESTED - Line Sync timeout now reports error and blocks stim.
2021-12-29 Fix confocal sync GUI bug
    Confocal sync retrieved the current limit from the LED index +1 - this +1 offset was removed.
2021-12-29 Implemented proper timeout when line clock is lost
    When shutter first opens - driver will wait 1 second for first line sync or will time out. After first sync is causght - driver will wait two mirror periods for each line sync or will time out. Drive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
2022-06-22 DMD custom sync
2022-07-29 Master GUI ported to High Current
2022-08-14 Custom sync working draft
2022-08-15 Switch from SD.h to SdFat.h
    SD.h was bugging out, including crashing on reading sequence files >5200 lines. so the code was ported over to the up-to-date SdFat library.
2022-08-17 Porting master confocal sync fix to high current
2022-09-06 Update pin
2022-09-08 Fix PWM error in custom
2022-09-13 Custom sync compiles
2022-09-13 Add custom sync folder to high current branch
2022-09-21 Add ignore Pyc, Add shutter check on trigger
    In case the shutter changes and then mirror stops, add a shutter check to confocal trigger sync so that trigger doesn't time out.
2022-11-09 Add padding to check channel timer to prevent lockup
2023-11-10 Add horn switch
2024-04-05 Add sync for hyperspectral DMD projection.
2026-02-20 Add BeRST/GCaMP6 Sync
2026-03-19 Add Teensy 4.1 to schematic
2026-03-28 minor tweaks
2026-06-18 More semiworking updates
2026-06-19 Connects and runs!!!
2026-06-19 Questionable AI revisions that did not solve actual PWM issue (which was the SD card)
2026-06-19 Fix pin issue
2026-06-23 Change magic_number clock frequency references - untested

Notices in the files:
KiCAD/Four Channel MHz LED Driver/Four Channel MHz LED Driver - high current.kicad_pcb:
License: Creative Commons Attribution-ShareAlike 4.0
parts and their libraries:
Copyright 2016 Accelerated Designs. All rights reserved.
